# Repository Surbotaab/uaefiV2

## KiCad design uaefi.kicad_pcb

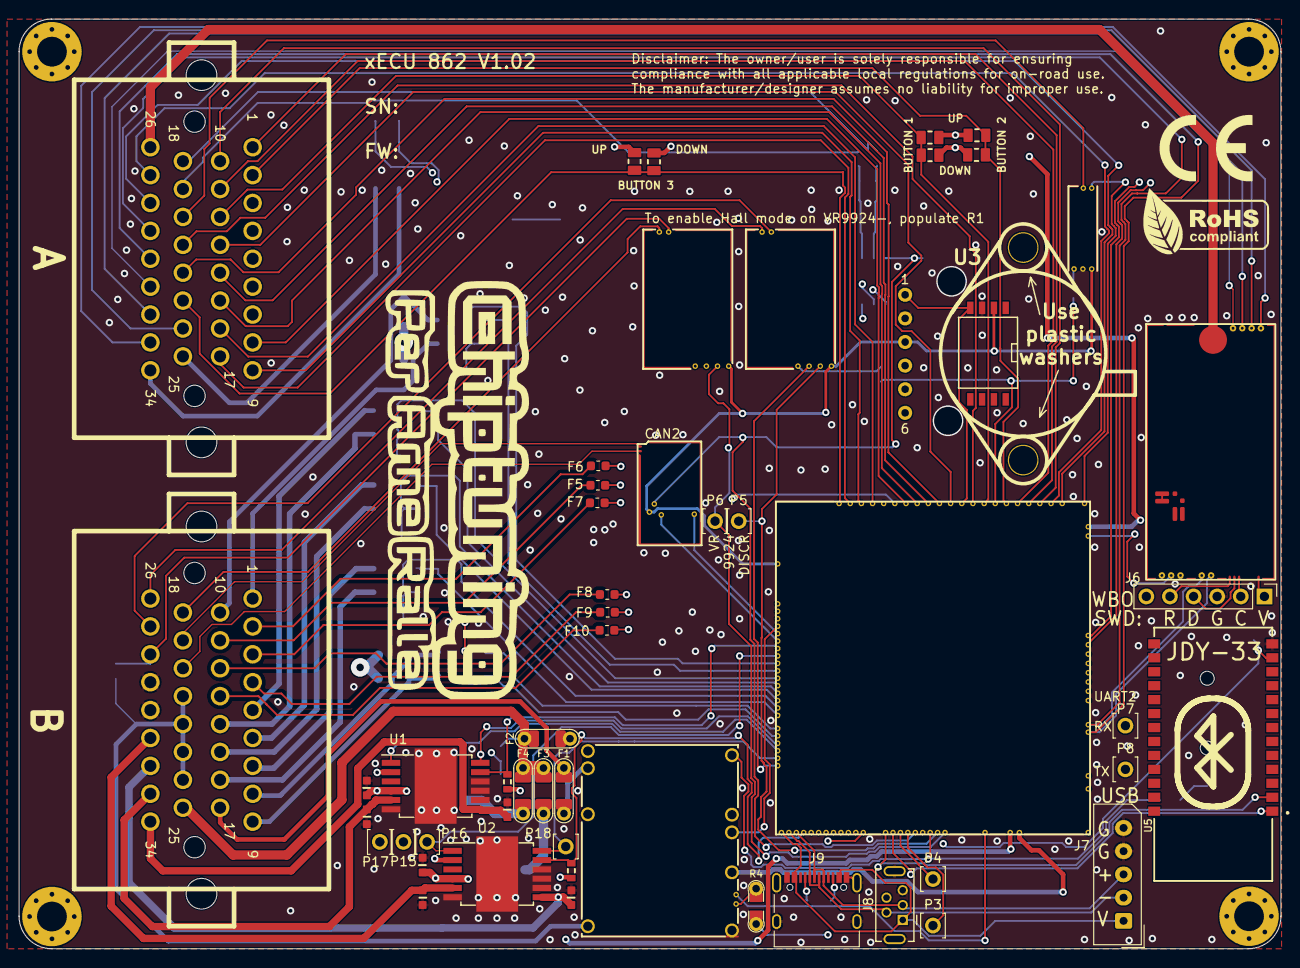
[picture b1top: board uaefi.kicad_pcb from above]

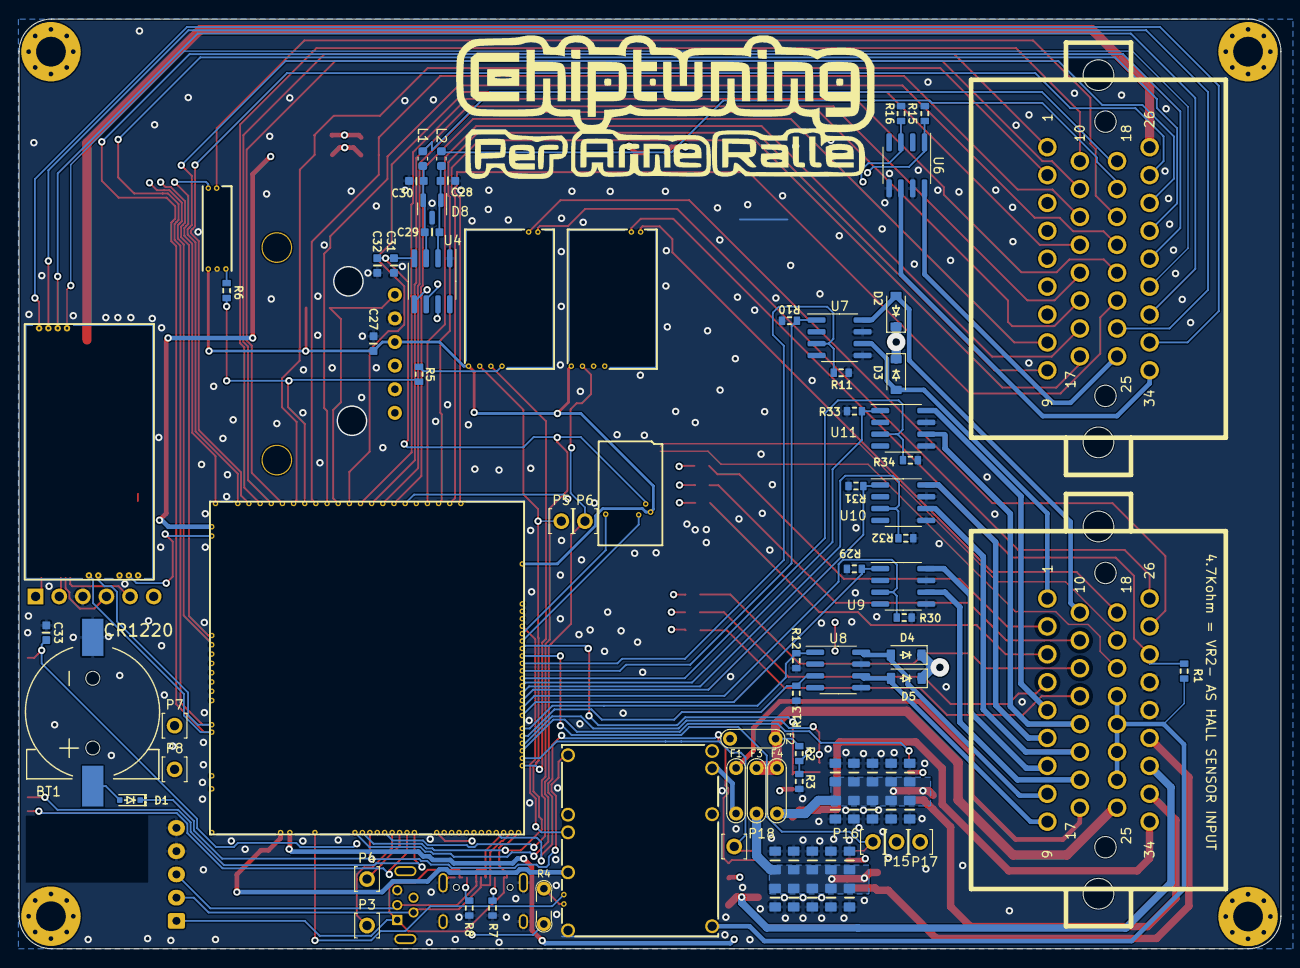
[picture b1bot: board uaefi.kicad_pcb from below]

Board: 4 copper layers, 135.7 x 100.0 mm, 118 parts (62 on the bottom side), 128 nets.

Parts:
BT1: CR1220; CR1220-2
C1, C2, C3, C4, C5, C6, C7, C8, C9, C10, C14, C15, C16, C17, C18, C19, C20, C21, C22, C23: 10u; C0805
C11, C24, C27, C29, C31, C33: 100n; C0603
C12, C13, C25, C26, C28, C30: 10n; C0603
C32: 1u; C0603
D1: 1N4148WS; SOD-323
D2, D3, D4, D5: B5819W; SOD-123
D8: NUP2105L; SOT-23
F1, F2, F3, F4: 12H1500D; PAD-1206-PAD
F5, F6, F7, F8, F9, F10: 50mA; Fuse_0603_1608Metric
H1, H2, H3, H4: M3; MountingHole_3.2mm_M3_Pad_Via
J6: Conn_01x06; PinHeader_1x06_P2.54mm_Vertical
J7: Conn_01x05_Male; Molex_SPOX_5267-05A_1x05_P2.50mm_Vertical
J8: USB_B_Mini; USB-MINI-B-VERTICAL
J9: USB_C
J23, J25: 2-6447232-3; TE 2-6447232-3
L1, L2: 470R@100MHz; L_0603_1608Metric
M1: Module-power_12and5V-0.3; power_12and5V
M2: Module-knock-0.2; knock
M3: Module-vr-discrete-0.5; vr-discrete
M4: Module-vr-max9924-0.1; vr-max9924
M5: Module-wbo-0.5; wbo
M6: Module:mega-mcu100/0.3; mega-mcu100
M7: Module-can-0.1; can
P3, P4, P5, P6, P7, P8, P15, P16, P17, P18: Pad; PAD-TH
R1, R9, R10, R11, R12, R13, R14, R15, R16, R29, R30, R31, R32, R33, R34: 4.7k; R0603
R2: 33k; R0603
R3: 6.8k; R0603
R4: Jumper-Pad-Pad; PAD-0805-PAD
R5, R6: 0; R0603
R7, R8: 5.6k; R0603
R35, R36, R37: 10k; R0805
R38, R39, R40: DNP; R0805
U1, U2: TLE9201SG; Infineon_PG-DSO-12-11
U3: MPX4/MPXH6400_MAP; MPX-4_MAP
U4: MAX31855KASA; SOIC-8_3.9x4.9mm_P1.27mm
U5: JDY-33
U6, U7, U8, U9, U10, U11: VNLD5160TR-E; SOIC-8_3.9x4.9mm_P1.27mm

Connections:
12V_KEY: F1.1, J23.17
+3.3V: M6.N21 (V33), R9.2, R14.2, U1.2 (VSO), U2.2 (VSO)
+3.3VA: C31.2, C32.2, C33.2, M6.N15 (V33_SWITCHABLE), M7.V2 (CAN_VIO), U4.4 (V_CC), U5.12 (3V3)
+5V: M1.E4 (V5), M6.N22 (VCC)
+5VA: C27.2, M2.E1 (V5A), M3.E4 (V5_IN), M4.E4 (V5_IN), M5.W1 (V5_IN), M6.E1 (V5A_SWITCHABLE), M6.W2 (V5A_SWITCHABLE), M7.V1 (V5), R38.2, R39.2, R40.2, U3.3 (VCC)
+5VP: J23.21, J23.22, J23.23, J23.24, M1.V4 (5VP), R1.1
+12V: F2.1, F3.1, F4.1, J23.25, R2.2
+12V_RAW: D2.1 (K), D3.1 (K), D4.1 (K), D5.1 (K), F2.2, M1.V1 (V12_PERM), M1.V3 (V12_RAW)
/ADC3: M6.S15 (IN_KNOCK_(PA2)), R5.2, R6.2
/CAN+: J25.29, M5.W4 (CANH), M6.W11 (CANH)
/CAN-: J25.30, M5.W3 (CANL), M6.W12 (CANL)
/DC1_DIR: M6.E21 (OUT_PWM4_(PC8)), P15.1, U1.1 (DIR)
/DC1_DIS: M6.E8 (SPI2_MISO_(PB14)), R9.1, U1.11 (DIS)
/DC1_PWM: M6.E20 (OUT_PWM3_(PC7)), P17.1, U1.12 (PWM)
/DC2_DIR: M6.E9 (SPI2_MOSI_(PB15)), P16.1, U2.1 (DIR)
/DC2_DIS: M6.N4 (USBID_(PA10)), R14.1, U2.11 (DIS)
/DC2_PWM: M6.E22 (OUT_PWM5_(PC9)), P18.1, U2.12 (PWM)
/DC Driver 1/PWR: C1.2, C2.2, C3.2, C4.2, C5.2, C6.2, C7.2, C8.2, C9.2, C10.2, C11.2, F4.2, U1.4 (VS)
/DC Driver 2/PWR: C14.2, C15.2, C16.2, C17.2, C18.2, C19.2, C20.2, C21.2, C22.2, C23.2, C24.2, F3.2, U2.4 (VS)
/EGT+: J25.18, L1.1
/EGT-: J25.19, L2.1
/EGT/SPI_CS: M6.N9 (SPI3_CS_(PA15)), U4.6 (~CS)
/IGN1: F6.2, M6.W10 (IGN1_(PC13))
/IGN2: F5.2, M6.W9 (IGN2_(PE5))
/IGN3: F7.2, M6.W8 (IGN3_(PE4))
/IGN4: F8.2, M6.W7 (IGN4_(PE3))
/IGN5: F9.2, M6.W6 (IGN5_(PE2))
/IGN6: F10.2, M6.W5 (IGN6_(PB8))
/INJ1: M6.E17 (OUT_INJ1_(PD3)), R29.2, U9.1 (IN1)
/INJ2: M6.E16 (OUT_INJ2_(PA9)), R30.2, U9.3 (IN2)
/INJ3: M6.E15 (OUT_INJ3_(PD11)), R31.2, U10.1 (IN1)
/INJ4: M6.E14 (OUT_INJ4_(PD10)), R32.2, U10.3 (IN2)
/INJ5: M6.E13 (OUT_INJ5_(PD2)), R33.2, U11.1 (IN1)
/INJ6: M6.E12 (OUT_INJ6_(PA8)), R34.2, U11.3 (IN2)
/INTERNAL_MAP: M6.S12 (IN_MAP2_(PC1)), U3.1 (VOUT)
/IN_AUX1: J25.13, M6.S11 (IN_O2S_/_CAN_WAKEUP_(PA0))
/IN_AUX2: J25.22, M6.S10 (IN_O2S2_(PA1))
/IN_AUX3: J25.8, M6.S7 (IN_AUX3_(PA7))
/IN_BUTTON1: J25.12, M6.S14 (IN_CRANK_(PB1)), R35.2, R38.1
/IN_BUTTON2: J25.2, M6.S16 (IN_CAM_(PA6)), R36.2, R39.1
/IN_BUTTON3: J25.23, M6.S1 (IN_D4_(PE15)), R37.2, R40.1
/IN_CLT: J25.28, M6.S21 (IN_CLT_(PC2))
/IN_FLEX: J25.11, M6.S17 (IN_VSS_(PE11))
/IN_HALL1: J25.16, M6.S4 (IN_D1_(PE12))
/IN_HALL2: J25.9, M6.S3 (IN_D2_(PE13))
/IN_HALL3: J25.17, M6.S2 (IN_D3_(PE14))
/IN_IAT: J25.27, M6.S20 (IN_IAT_(PC3))
/IN_KNOCK: M2.E3 (OUT_KNOCK), R6.1
/IN_KNOCK_RAW: J25.20, M2.W1 (IN_KNOCK)
/IN_PPS1: J25.10, M6.S19 (IN_PPS_(PA3))
/IN_PPS2: J25.15, M6.S8 (IN_AUX2_(PC4/PE9))
/IN_TPS1: J25.1, M6.S18 (IN_TPS_(PA4))
/IN_TPS2: J25.14, M6.S9 (IN_AUX1_(PB0))
/IN_VIGN: F1.2, M1.V2 (IN_VIGN)
/IN_VMAIN: M6.S6 (IN_AUX4_(PC5)), R2.1, R3.2
/LS1: M6.E11 (OUT_INJ7_(PD15)), R10.2, U7.1 (IN1)
/LS2: M6.E10 (OUT_INJ8_(PD12)), R11.2, U7.3 (IN2)
/LS3: M6.E18 (OUT_PWM1_(PD13)), R12.2, U8.1 (IN1)
/LS4: M6.E19 (OUT_PWM2_(PC6)), R13.2, U8.3 (IN2)
/LS_HOT1: M6.W4 (IGN7_(PB9)), R16.1, U6.3 (IN2)
/LS_HOT2: M6.W3 (IGN8_(PE6)), R15.1, U6.1 (IN1)
/MISO3: M6.N11 (SPI3_MISO_(PC11)), U4.7 (SO)
/OUT_DC1+: C13.2, J23.34, U1.7 (OUT2)
/OUT_DC1-: C12.2, J23.33, U1.5 (OUT1)
/OUT_DC2+: C26.2, J23.32, U2.7 (OUT2)
/OUT_DC2-: C25.2, J23.31, U2.5 (OUT1)
/OUT_IGN1: F6.1, J23.2
/OUT_IGN2: F5.1, J23.11
/OUT_IGN3: F7.1, J23.3
/OUT_IGN4: F8.1, J23.12
/OUT_IGN5: F9.1, J23.4
/OUT_IGN6: F10.1, J23.13
/OUT_INJ1: J23.7, U9.8 (D1)
/OUT_INJ2: J23.16, U9.6 (D2)
/OUT_INJ3: J23.6, U10.8 (D1)
/OUT_INJ4: J23.15, U10.6 (D2)
/OUT_INJ5: J23.5, U11.8 (D1)
/OUT_INJ6: J23.14, U11.6 (D2)
/OUT_LS1: D2.2 (A), J23.10, U7.8 (D1)
/OUT_LS2: D3.2 (A), J23.1, U7.6 (D2)
/OUT_LS3: D4.2 (A), J23.8, U8.8 (D1)
/OUT_LS4: D5.2 (A), J23.9, U8.6 (D2)
/OUT_LS_HOT1: J25.34, U6.6 (D2)
/OUT_LS_HOT2: J25.25, U6.8 (D1)
/PG_5VP: M6.N12 (SPI3_MOSI_(PC12)), R4.2
/PWR_EN: M1.E5 (EN_5VP), M6.N20 (OUT_PWR_EN_(PE10))
/SCK3: M6.N10 (SPI3_SCK_(PC10)), U4.5 (SCK)
/USB+: J7.3, J8.3 (D+), J9.A6 (D+), J9.B6 (D+), M6.N3 (USBP_(PA12))
/USB-: J7.2, J8.2 (D-), J9.A7 (D-), J9.B7 (D-), M6.N2 (USBM_(PA11))
/VBAT: D1.1 (K), M1.E1 (VBAT), M6.N17 (VBAT)
/VBUS: J7.1, J8.1 (VBUS), J9.A4 (VBUS), J9.A9 (VBUS), J9.B4 (VBUS), J9.B9 (VBUS), M6.N1 (VBUS)
/VIGN: M1.E3 (VIGN), M6.E5 (IN_VIGN_(PA5))
/VREF1: M2.W2 (VREF), M6.S22 (VREF1)
/VR_DISCRETE: M3.E3 (OUT), M6.N18 (UART8_RX_(PE0)), P5.1
/VR_DISCRETE+: J23.26, M3.W2 (VR+)
/VR_DISCRETE-: J23.27, M3.W1 (VR-)
/VR_DISCRETE_A: M3.E2 (OUT_A), R5.1
/VR_DISCRETE_THR: M3.E1 (Thresh_IN), M6.E23 (OUT_PWM6_(PD14))
/VR_MAX9924: M4.E3 (OUT), M6.N19 (UART8_TX_(PE1)), P6.1
/VR_MAX9924+: J23.18, M4.W2 (VR+)
/VR_MAX9924-: J23.28, M4.W1 (VR-), R1.2
/WBO_Heater: J25.26, M5.E5 (LSU_H+)
/WBO_Ip: J25.32, M5.E3 (LSU_Ip)
/WBO_Rtrim: J25.24, M5.E4 (LSU_Rtrim)
/WBO_Un: J25.33, M5.E1 (LSU_Un)
/WBO_Vm: J25.31, M5.E2 (LSU_Vm)
CAN2H: J23.20, M7.S2 (CANH)
CAN2L: J23.19, M7.S1 (CANL)
GND: BT1.2 (-), C1.1, C2.1, C3.1, C4.1, C5.1, C6.1, C7.1, C8.1, C9.1, C10.1, C11.1, C12.1, C13.1, C14.1, C15.1, C16.1, C17.1, C18.1, C19.1, C20.1, C21.1, C22.1, C23.1, C24.1, C25.1, C26.1, C27.1, C28.1, C30.1, C31.1, C32.1, C33.1, D8.3 (A), J6.3, J7.4, J7.5, J8.5 (GND), J8.6 (Shield), J9.A1 (GND), J9.A12 (GND), J9.B1 (GND), J9.B12 (GND), J9.S1 (SHIELD), J23.29, J23.30, M1.S1 (GND), M2.E2 (GND), M3.G (GND), M4.G (GND), M5.E6 (LSU_H-), M5.G (GND), M6.G (GND), M7.E1 (GND), R3.1, R7.1, R8.1, R10.1, R11.1, R12.1, R13.1, R15.2, R16.2, R29.1, R30.1, R31.1, R32.1, R33.1, R34.1, U1.6 (GND), U1.8 (SI), U1.9 (CSN), U1.10 (SCK), U1.13 (GND), U2.6 (GND), U2.8 (SI), U2.9 (CSN), U2.10 (SCK), U2.13 (GND), U3.2 (GND), U4.1 (GND), U5.13 (GND), U6.5 (S2), U6.7 (S1), U7.5 (S2), U7.7 (S1), U8.5 (S2), U8.7 (S1), U9.5 (S2), U9.7 (S1), U10.5 (S2), U10.7 (S1), U11.5 (S2), U11.7 (S1)
GNDA: J25.3, J25.4, J25.5, J25.6, J25.7, M6.W1 (GNDA), R35.1, R36.1, R37.1
IN_MAP: J25.21, M6.S13 (IN_MAP1_(PC0))
unnamed: BT1.1 (+), D1.2 (A)
unnamed: J6.1, M5.W8 (V33_OUT)
unnamed: J6.2, M5.W7 (SWCLK)
unnamed: J6.4, M5.W6 (SWDIO)
unnamed: J6.5, M5.W5 (nReset)
unnamed: J9.A5 (CC1), R7.2
unnamed: J9.B5 (CC2), R8.2
unnamed: M1.E6 (PG_5VP), R4.1
unnamed: M5.J1 (SEL1), M5.J_GND1 (PULL_DOWN1)
unnamed: M6.N14a (LED_GREEN), P4.1
unnamed: M6.N14b (LED_YELLOW), P3.1
unnamed: M6.E6 (SPI2_CS_/_CAN2_RX_(PB12)), M7.V6 (CAN_RX)
unnamed: M6.E7 (SPI2_SCK_/_CAN2_TX_(PB13)), M7.V5 (CAN_TX)
unnamed: M6.N14 (UART2_RX_(PD6)), P7.1, U5.1 (TXD)
unnamed: M6.N13 (UART2_TX_(PD5)), P8.1, U5.2 (RXD)
unnamed: C29.2, C30.2, D8.2 (K), L1.2, U4.3 (T+)
unnamed: C28.2, C29.1, D8.1 (K), L2.2, U4.2 (T-)

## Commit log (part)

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2025-10-13 a
    c
2025-10-13 s
    df
2025-10-13 [skip actions] Auto-generated board v2.1
2025-10-13 AAa
    AA
2025-10-13 mkn
    mnj
2025-10-24 A
    AAA
2025-10-26 Final?
2025-10-26 aaaaa
2025-10-26 vefsjl
2025-10-26 ghjk
2025-11-03 Final marking
2025-11-05 Prod Candidate 1
2025-11-06 GHA says update hellen-one
2025-11-12 test
2025-12-08 reset
2026-01-21 a
    b
2026-01-21 a
    A
